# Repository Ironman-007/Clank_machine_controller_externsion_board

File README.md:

# Clank_machine_controller_externsion_board

The Clank machine controller externsion board design, the functions include:

- Limit switch connections;
- Power supply & control;
- Spindle motor control module;

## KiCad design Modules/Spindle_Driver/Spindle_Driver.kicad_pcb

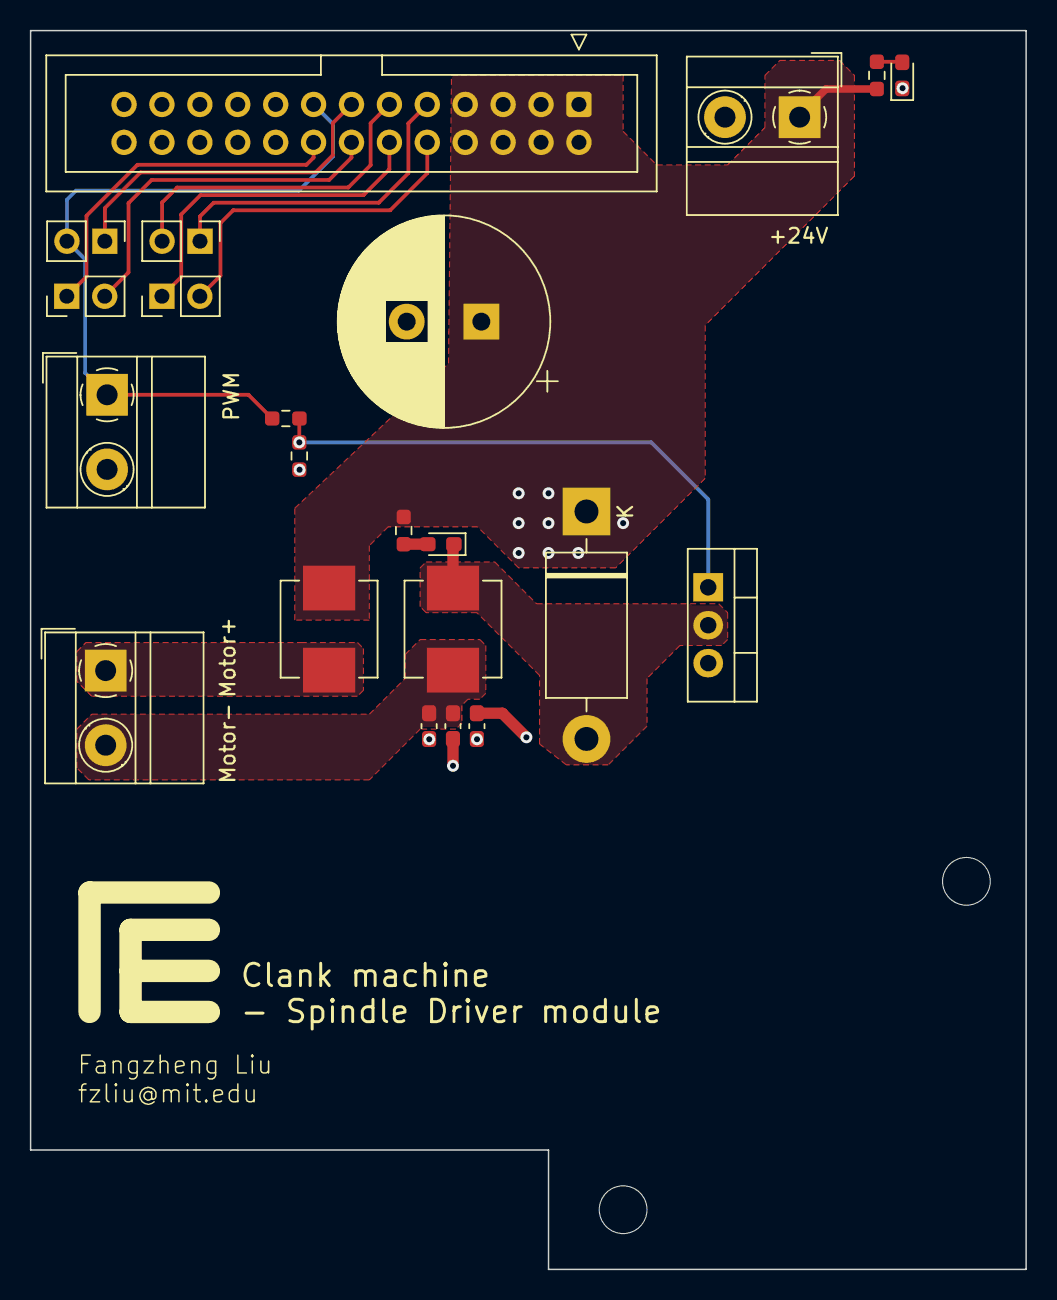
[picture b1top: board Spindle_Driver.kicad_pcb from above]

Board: 2 copper layers, 66.7 x 83.0 mm, 24 parts (0 on the bottom side), 16 nets.

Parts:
C1: 220uF; CP_Radial_D14.0mm_P5.00mm
C2, C3, C4: 0.1uF; C_0603_1608Metric_Pad1.08x0.95mm_HandSolder
D1: 1N5822; D_DO-201AD_P15.24mm_Horizontal
D2, D3: LED; LED_0603_1608Metric_Pad1.05x0.95mm_HandSolder
H1, H2: M3; MountingHole_3.2mm_M3
J1: PWR in; TerminalBlock_MetzConnect_Type011_RT05502HBWC_1x02_P5.00mm_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
J3: Ctrl in; TerminalBlock_MetzConnect_Type011_RT05502HBWC_1x02_P5.00mm_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
J4: To Spindle; TerminalBlock_MetzConnect_Type011_RT05502HBWC_1x02_P5.00mm_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
J5, J6, J7, J9: +5V Conn; PinHeader_1x02_P2.54mm_Vertical
J8: Conn_02x13_Odd_Even; IDC-Header_2x13_P2.54mm_Vertical
L1, L2: 3.3uH; SRP7028A-3R3M
Q1: IRF540N; TO-220-3_Vertical
R1, R3, R4: 10K; R_0603_1608Metric_Pad0.98x0.95mm_HandSolder
R2: 150; R_0603_1608Metric_Pad0.98x0.95mm_HandSolder

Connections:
+24V: C1.1, C2.1, C3.1, D1.1 (K), J1.1, J8.1, J8.2, J8.3, J8.4, J8.5, J8.6, J8.7, J8.8, L1.1, R1.2, R4.2
/Motor+: J4.1, L1.2
/Motor-: C3.2, C4.1, J4.2, L2.2
/PWM: J3.1, J7.2, J8.15, R2.1
/net_D: D1.2 (A), D2.1 (K), L2.1, Q1.2 (D)
GND: C1.2, C2.2, C4.2, D3.1 (K), J1.2, J3.2, J8.17, J8.18, J8.19, J8.20, J8.21, J8.22, J8.23, J8.24, J8.25, J8.26, Q1.3 (S), R3.1
unnamed: D2.2 (A), R1.1
unnamed: D3.2 (A), R4.1
unnamed: J5.1, J8.9
unnamed: J5.2, J8.11
unnamed: J6.1, J8.12
unnamed: J6.2, J8.10
unnamed: J7.1, J8.13
unnamed: J8.14, J9.2
unnamed: J8.16, J9.1
unnamed: Q1.1 (G), R2.2, R3.2

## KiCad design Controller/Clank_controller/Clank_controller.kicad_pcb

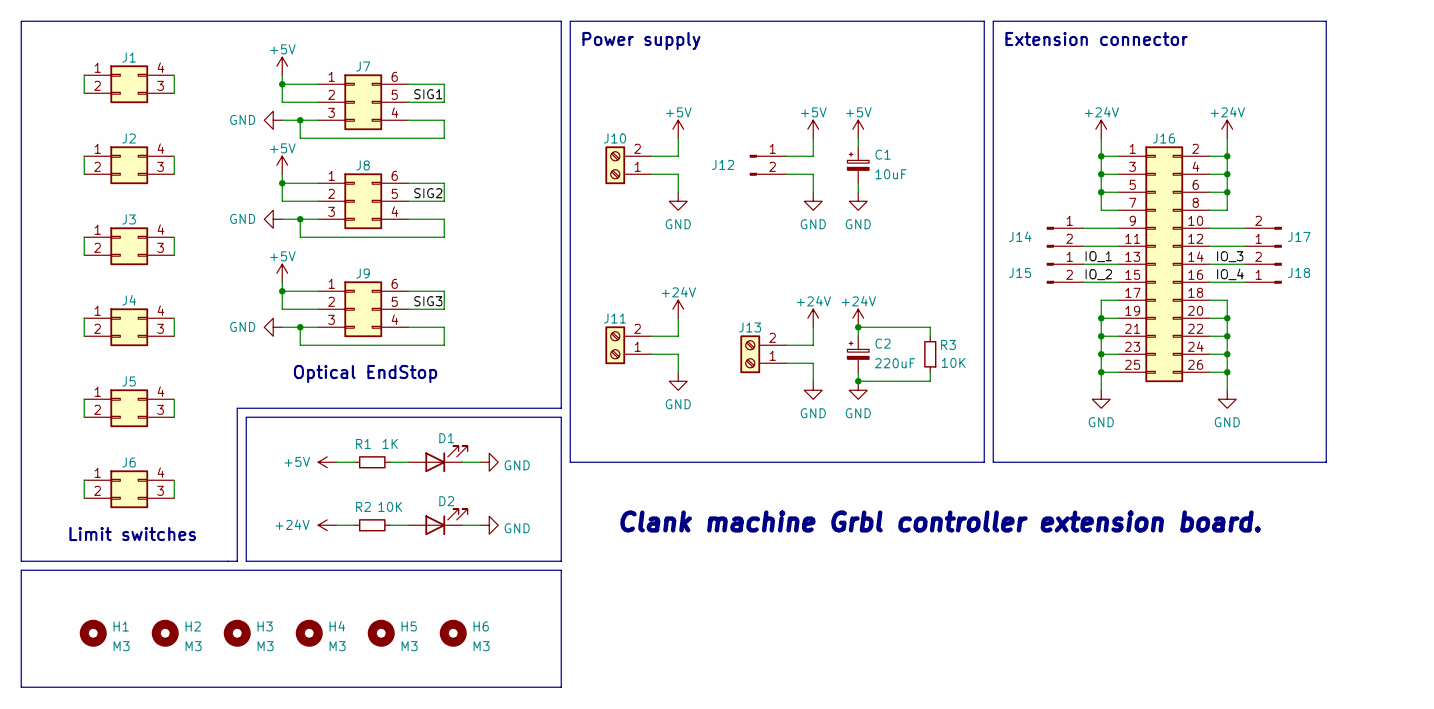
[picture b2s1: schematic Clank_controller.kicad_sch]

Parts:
C1: 10uF; CP_Radial_D5.0mm_P2.50mm
C2: 220uF; CP_Radial_D14.0mm_P5.00mm
D1, D2: LED; LED_1206_3216Metric_Pad1.42x1.75mm_HandSolder
H1, H2, H3, H4, H5, H6: M3; MountingHole_3.2mm_M3
J1, J2, J3, J4, J5, J6: Limit_SW; PinHeader_2x02_P2.54mm_Vertical
J7, J8, J9: Conn_02x03_Counter_Clockwise; PinHeader_2x03_P2.54mm_Vertical
J10, J11, J13: Screw_Terminal_01x02; TerminalBlock_MetzConnect_Type011_RT05502HBWC_1x02_P5.00mm_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
J12, J14, J15, J17, J18: +5V Conn; PinHeader_1x02_P2.54mm_Vertical
J16: Conn_02x13_Odd_Even; IDC-Header_2x13_P2.54mm_Vertical
R1: 1K; R_1206_3216Metric_Pad1.30x1.75mm_HandSolder
R2, R3: 10K; R_1206_3216Metric_Pad1.30x1.75mm_HandSolder

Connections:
+5V: C1.1, J7.1, J7.2, J8.1, J8.2, J9.1, J9.2, J10.2, J12.1, R1.1
+24V: C2.1, J11.2, J13.2, J16.1, J16.2, J16.3, J16.4, J16.5, J16.6, J16.7, J16.8, R2.1, R3.2
/IO_1: J15.1, J16.13
/IO_2: J15.2, J16.15
/IO_3: J16.14, J18.2
/IO_4: J16.16, J18.1
/SIG1: J7.5, J7.6
/SIG2: J8.5, J8.6
/SIG3: J9.5, J9.6
GND: C1.2, C2.2, D1.1 (K), D2.1 (K), J7.3, J7.4, J8.3, J8.4, J9.3, J9.4, J10.1, J11.1, J12.2, J13.1, J16.17, J16.18, J16.19, J16.20, J16.21, J16.22, J16.23, J16.24, J16.25, J16.26, R3.1
unnamed: D1.2 (A), R1.2
unnamed: D2.2 (A), R2.2
unnamed: J1.1, J1.2
unnamed: J1.3, J1.4
unnamed: J2.1, J2.2
unnamed: J2.3, J2.4
unnamed: J3.1, J3.2
unnamed: J3.3, J3.4
unnamed: J4.1, J4.2
unnamed: J4.3, J4.4
unnamed: J5.1, J5.2
unnamed: J5.3, J5.4
unnamed: J6.1, J6.2
unnamed: J6.3, J6.4
unnamed: J14.1, J16.9
unnamed: J14.2, J16.11
unnamed: J16.10, J17.2
unnamed: J16.12, J17.1

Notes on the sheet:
Extension connector
Limit switches
Clank machine Grbl controller extension board.
Power supply
Optical EndStop

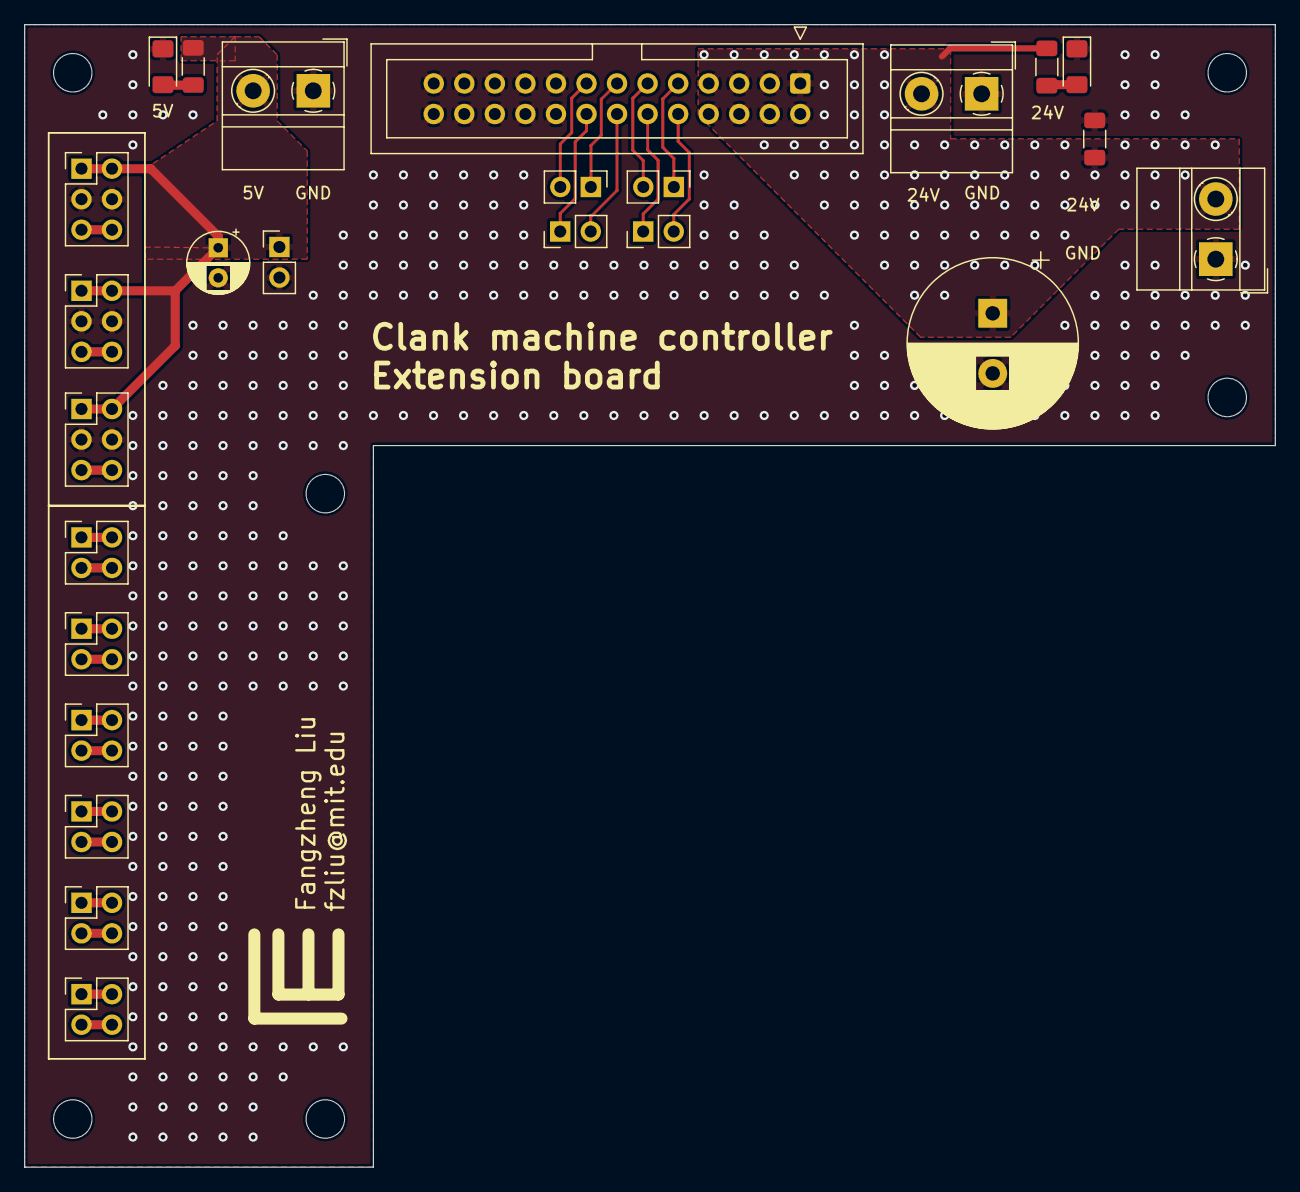
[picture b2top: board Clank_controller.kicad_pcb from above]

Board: 2 copper layers, 104.0 x 95.0 mm, 31 parts (0 on the bottom side), 28 nets.

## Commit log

2023-01-12 udated by FZ
